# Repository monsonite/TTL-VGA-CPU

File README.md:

# TTL-VGA-CPU
EagleCAD schematics and layout of Marcel van Kervinck's TTL VGA Computer

This is an 8-bit Harvard architecture cpu developed by Marcel van Kervinck - as a practical CPU using simple TTL logic to create a VGA display of 160 x120 pixels in 6-bit colour.

Marcel's original design may be found on HackaDay here: https://hackaday.io/project/20781-8-bit-color-computer-from-ttl

The aim was to develop a practical 8-bit CPU using a minimum of TTL packages - with emphasis on using only those parts that are commonly available.

This repository begins with a transcription of his design to EagleCAD so that the circuit schematic may be better understood and different layout options evaluated.

Marcel has produced a pcb for his design using KiCAD - approximately 9"x6".  However it may be feasible to get the design onto a more compact 6"x4" Eurocard - especially if SMT TTL parts are used.

The files here are in a draft form and are missing some key control signals. They are for information only and do not currently represent a 100% complete transcript of Marcel's design.

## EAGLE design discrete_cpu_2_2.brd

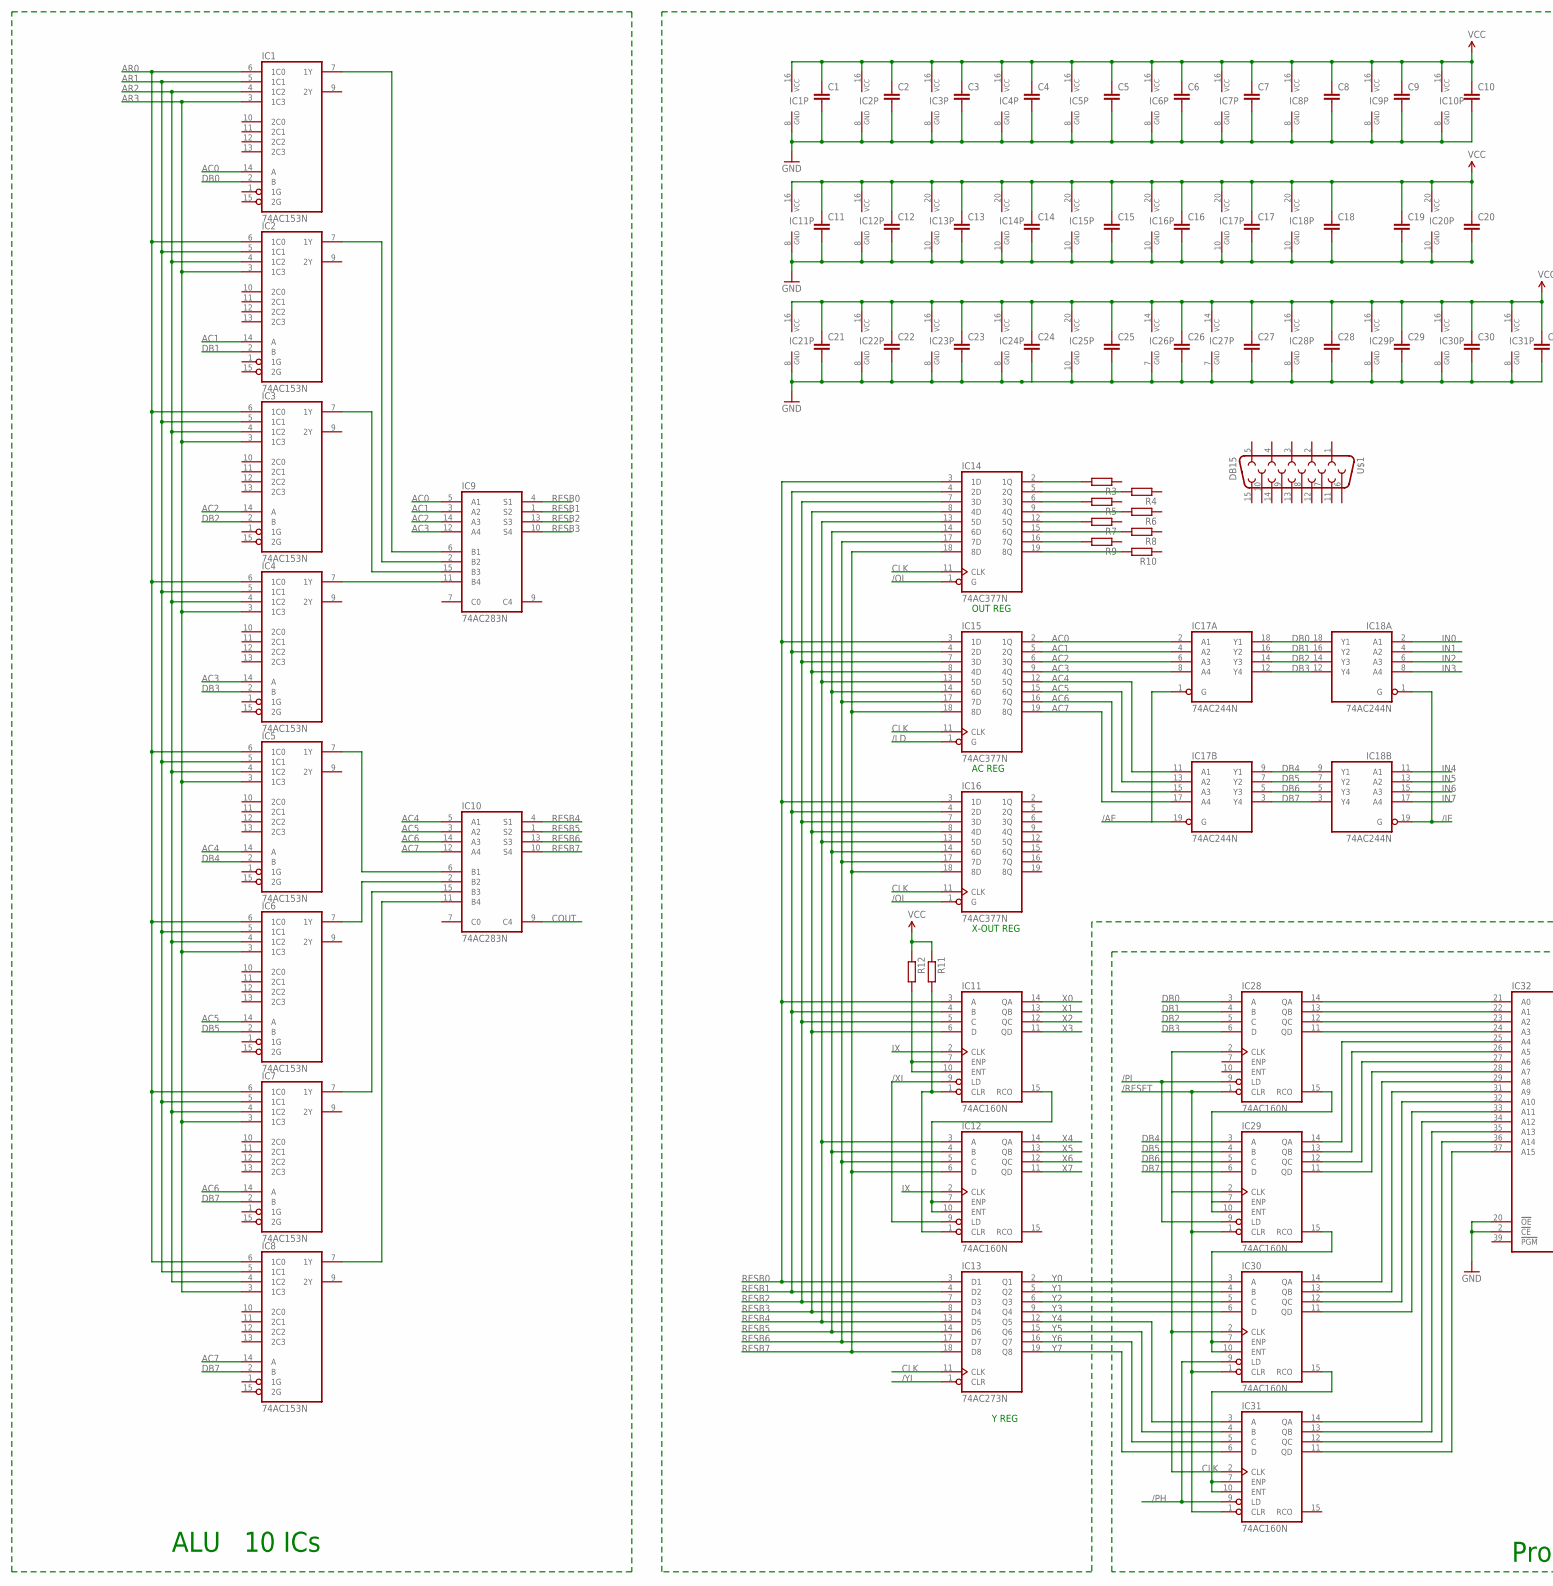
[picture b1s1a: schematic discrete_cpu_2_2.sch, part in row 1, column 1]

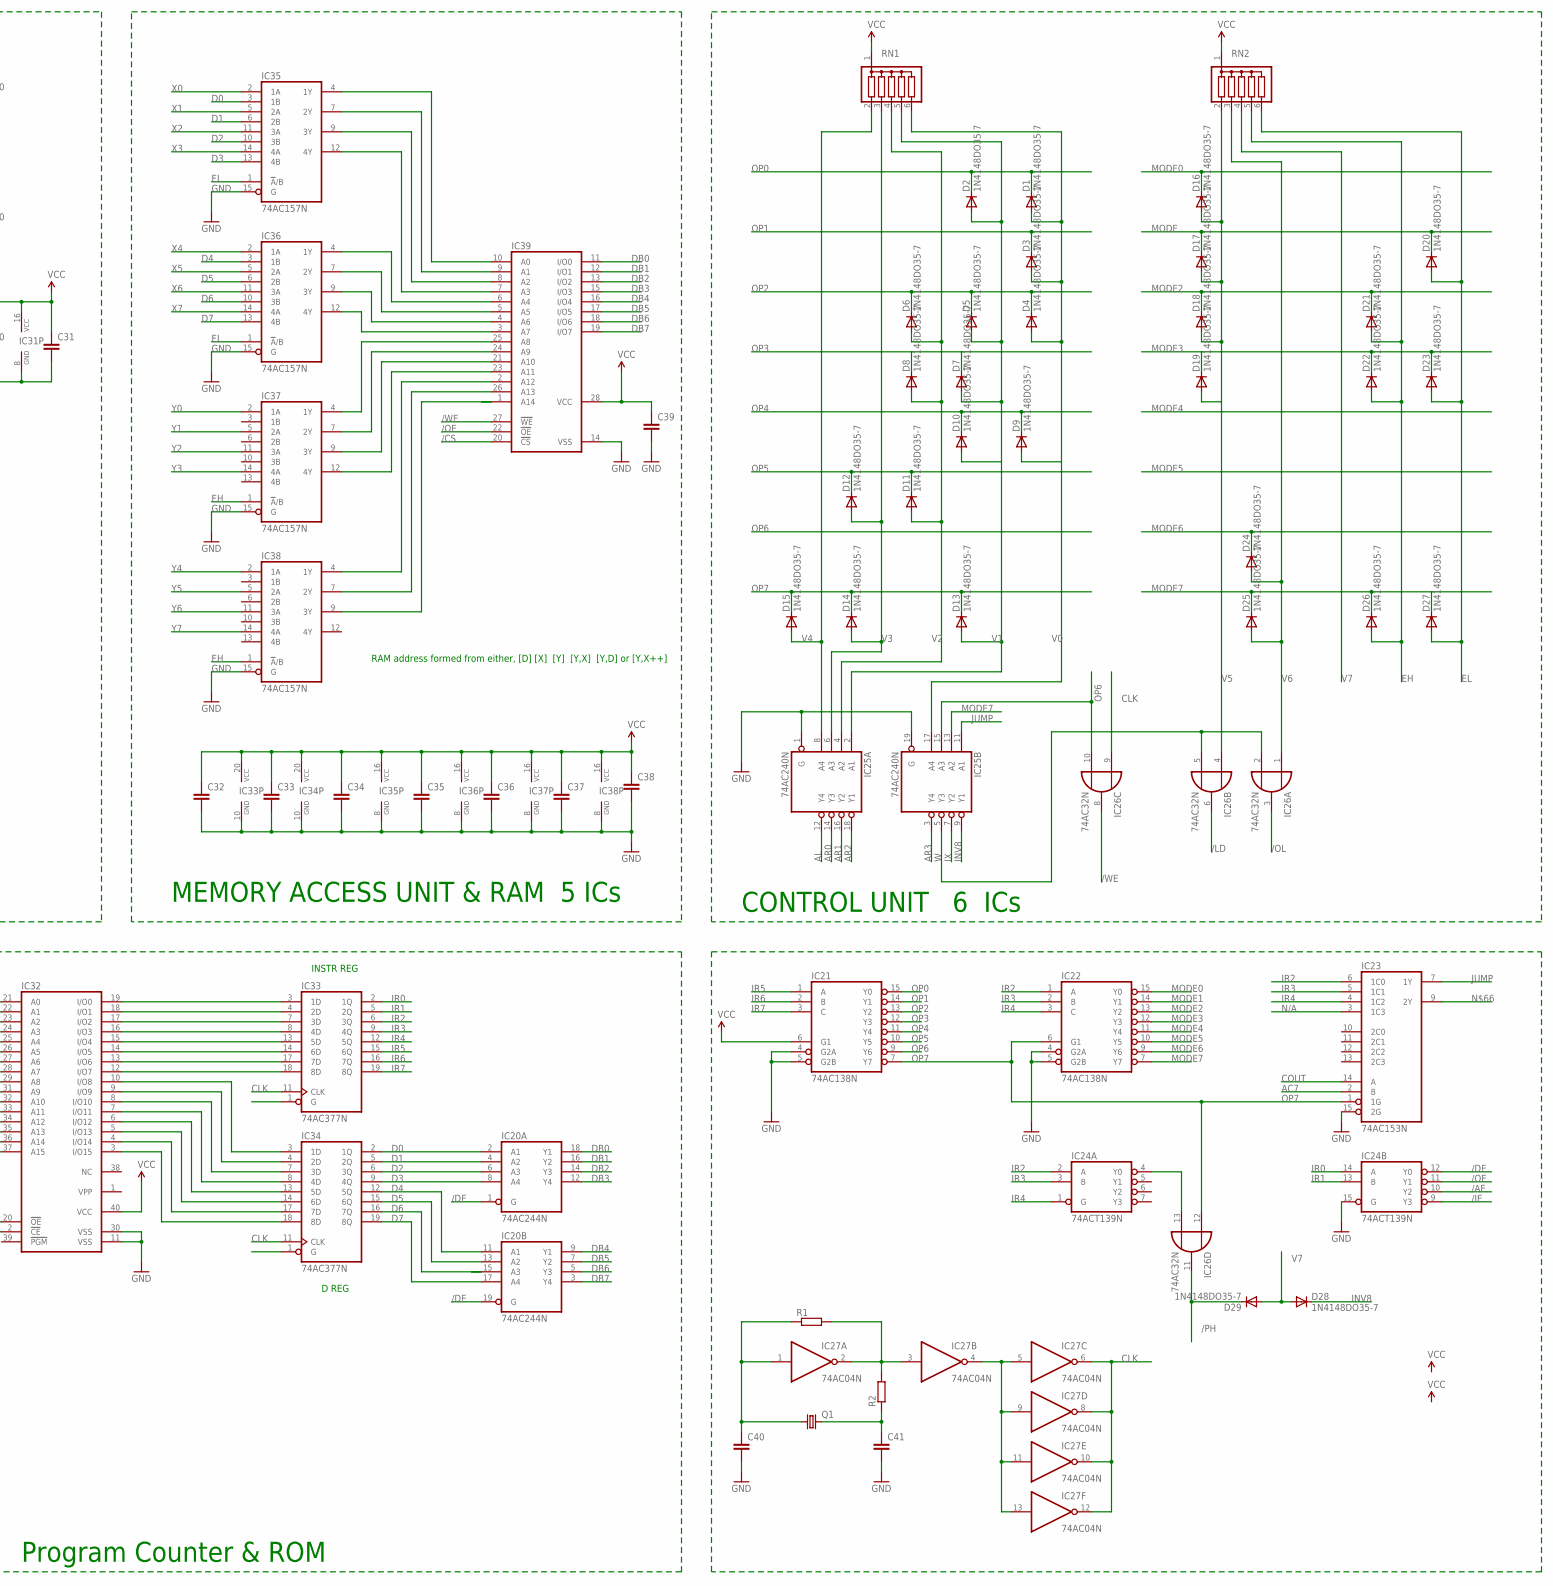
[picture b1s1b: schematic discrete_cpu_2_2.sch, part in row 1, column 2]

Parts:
C1, C2, C3, C4, C5, C6, C7, C8, C9, C10, C11, C12, C13, C14, C15, C16, C17, C18, C19, C20, C21, C22, C23, C24, C25, C26, C27, C28, C29, C30, C31, C32, C33, C34, C35, C36, C37, C38, C39, C40, C41: C-EU025-025X050; C025-025X050
D1, D2, D3, D4, D5, D6, D7, D8, D9, D10, D11, D12, D13, D14, D15, D16, D17, D18, D19, D20, D21, D22, D23, D24, D25, D26, D27, D28, D29: 1N4148DO35-7; DO35-7
IC1, IC2, IC3, IC4, IC5, IC6, IC7, IC8, IC23: 74AC153N; DIL16
IC9, IC10: 74AC283N; DIL16
IC11, IC12, IC28, IC29, IC30, IC31: 74AC160N; DIL16
IC13: 74AC273N; DIL20
IC14, IC15, IC16, IC33, IC34: 74AC377N; DIL20
IC17, IC18, IC20: 74AC244N; DIL20
IC21, IC22: 74AC138N; DIL16
IC24: 74ACT139N; DIL16
IC25: 74AC240N; DIL20
IC26: 74AC32N; DIL14
IC27: 74AC04N; DIL14
IC32: 27C1024HG; DIL40
IC35, IC36, IC37, IC38: 74AC157N; DIL16
IC39: 62256P; DIL28-6
Q1: CRYSTALHC49S; HC49/S
R1, R2, R3, R4, R5, R6, R7, R8, R9, R10, R11, R12: R-EU_0204/7; 0204/7
RN1, RN2: G05R; SIL6
U$1: DB15

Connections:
/AE: IC17.1 (G), IC17.19 (G), IC24.10 (Y2)
/CS: IC39.20 (!CS)
/DE: IC20.1 (G), IC20.19 (G), IC24.12 (Y0)
/IE: IC18.1 (G), IC18.19 (G), IC24.9 (Y3)
/LD: IC15.1 (G), IC26.6 (O)
/OE: IC24.11 (Y1), IC39.22 (!OE)
/OL: IC14.1 (G), IC16.1 (G), IC26.3 (O)
/PH: D29.C, IC26.11 (O), IC30.9 (LD), IC31.9 (LD)
/PL: IC28.9 (LD), IC29.9 (LD)
/RESET: IC28.1 (CLR), IC29.1 (CLR), IC30.1 (CLR), IC31.1 (CLR)
/WE: IC26.8 (O), IC39.27 (!WE)
/XL: IC11.9 (LD), IC12.9 (LD)
/YL: IC13.1 (CLR)
AC0: IC1.14 (A), IC9.5 (A1), IC15.2 (1Q), IC17.2 (A1)
AC1: IC2.14 (A), IC9.3 (A2), IC15.5 (2Q), IC17.4 (A2)
AC2: IC3.14 (A), IC9.14 (A3), IC15.6 (3Q), IC17.6 (A3)
AC3: IC4.14 (A), IC9.12 (A4), IC15.9 (4Q), IC17.8 (A4)
AC4: IC5.14 (A), IC10.5 (A1), IC15.12 (5Q), IC17.11 (A1)
AC5: IC6.14 (A), IC10.3 (A2), IC15.15 (6Q), IC17.13 (A2)
AC6: IC7.14 (A), IC10.14 (A3), IC15.16 (7Q), IC17.15 (A3)
AC7: IC8.14 (A), IC10.12 (A4), IC15.19 (8Q), IC17.17 (A4), IC23.2 (B)
AL: IC25.12 (Y4)
AR0: IC1.6 (1C0), IC2.6 (1C0), IC3.6 (1C0), IC4.6 (1C0), IC5.6 (1C0), IC6.6 (1C0), IC7.6 (1C0), IC8.6 (1C0), IC25.14 (Y3)
AR1: IC1.5 (1C1), IC2.5 (1C1), IC3.5 (1C1), IC4.5 (1C1), IC5.5 (1C1), IC6.5 (1C1), IC7.5 (1C1), IC8.5 (1C1), IC25.16 (Y2)
AR2: IC1.4 (1C2), IC2.4 (1C2), IC3.4 (1C2), IC4.4 (1C2), IC5.4 (1C2), IC6.4 (1C2), IC7.4 (1C2), IC8.4 (1C2), IC25.18 (Y1)
AR3: IC1.3 (1C3), IC2.3 (1C3), IC3.3 (1C3), IC4.3 (1C3), IC5.3 (1C3), IC6.3 (1C3), IC7.3 (1C3), IC8.3 (1C3), IC25.3 (Y4)
CLK: IC13.11 (CLK), IC14.11 (CLK), IC15.11 (CLK), IC16.11 (CLK), IC26.9 (I0), IC27.6 (O), IC27.8 (O), IC27.10 (O), IC27.12 (O), IC28.2 (CLK), IC29.2 (CLK), IC30.2 (CLK), IC31.2 (CLK), IC33.11 (CLK), IC34.11 (CLK)
COUT: IC10.9 (C4), IC23.14 (A)
D0: IC20.2 (A1), IC34.2 (1Q), IC35.3 (1B)
D1: IC20.4 (A2), IC34.5 (2Q), IC35.6 (2B)
D2: IC20.6 (A3), IC34.6 (3Q), IC35.10 (3B)
D3: IC20.8 (A4), IC34.9 (4Q), IC35.13 (4B)
D4: IC20.11 (A1), IC34.12 (5Q), IC36.3 (1B)
D5: IC20.13 (A2), IC34.15 (6Q), IC36.6 (2B)
D6: IC20.15 (A3), IC34.16 (7Q), IC36.10 (3B)
D7: IC20.17 (A4), IC34.19 (8Q), IC36.13 (4B)
DB0: IC1.2 (B), IC17.18 (Y1), IC18.18 (Y1), IC20.18 (Y1), IC28.3 (A), IC39.11 (I/O0)
DB1: IC2.2 (B), IC17.16 (Y2), IC18.16 (Y2), IC20.16 (Y2), IC28.4 (B), IC39.12 (I/O1)
DB2: IC3.2 (B), IC17.14 (Y3), IC18.14 (Y3), IC20.14 (Y3), IC28.5 (C), IC39.13 (I/O2)
DB3: IC4.2 (B), IC17.12 (Y4), IC18.12 (Y4), IC20.12 (Y4), IC28.6 (D), IC39.15 (I/O3)
DB4: IC5.2 (B), IC17.9 (Y1), IC18.9 (Y1), IC20.9 (Y1), IC29.3 (A), IC39.16 (I/O4)
DB5: IC6.2 (B), IC17.7 (Y2), IC18.7 (Y2), IC20.7 (Y2), IC29.4 (B), IC39.17 (I/O5)
DB6: IC17.5 (Y3), IC18.5 (Y3), IC20.5 (Y3), IC29.5 (C), IC39.18 (I/O6)
DB7: IC7.2 (B), IC8.2 (B), IC17.3 (Y4), IC18.3 (Y4), IC20.3 (Y4), IC29.6 (D), IC39.19 (I/O7)
EH: D21.A, D22.A, D26.A, IC37.1 (!A!/B), IC38.1 (!A!/B), RN2.5
EL: D20.A, D23.A, D27.A, IC35.1 (!A!/B), IC36.1 (!A!/B), RN2.6
GND: C1.2, C2.2, C3.2, C4.2, C5.2, C6.2, C7.2, C8.2, C9.2, C10.2, C11.2, C12.2, C13.2, C14.2, C15.2, C16.2, C17.2, C18.2, C19.2, C20.2, C21.2, C22.2, C23.2, C24.2, C25.2, C26.2, C27.2, C28.2, C29.2, C30.2, C31.2, C32.2, C33.2, C34.2, C35.2, C36.2, C37.2, C38.2, C39.2, C40.2, C41.2, IC1.8 (GND), IC2.8 (GND), IC3.8 (GND), IC4.8 (GND), IC5.8 (GND), IC6.8 (GND), IC7.8 (GND), IC8.8 (GND), IC9.8 (GND), IC10.8 (GND), IC11.8 (GND), IC12.8 (GND), IC13.10 (GND), IC14.10 (GND), IC15.10 (GND), IC16.10 (GND), IC17.10 (GND), IC18.10 (GND), IC20.10 (GND), IC21.4 (G2A), IC21.5 (G2B), IC21.8 (GND), IC22.4 (G2A), IC22.5 (G2B), IC22.8 (GND), IC23.8 (GND), IC23.15 (2G), IC24.8 (GND), IC24.15 (G), IC25.1 (G), IC25.10 (GND), IC25.19 (G), IC26.7 (GND), IC27.7 (GND), IC28.8 (GND), IC29.8 (GND), IC30.8 (GND), IC31.8 (GND), IC32.2 (!CE), IC32.11 (VSS), IC32.20 (!OE), IC32.30 (VSS), IC33.10 (GND), IC34.10 (GND), IC35.8 (GND), IC35.15 (G), IC36.8 (GND), IC36.15 (G), IC37.8 (GND), IC37.15 (G), IC38.8 (GND), IC38.15 (G), IC39.14 (VSS)
IN0: IC18.2 (A1)
IN1: IC18.4 (A2)
IN2: IC18.6 (A3)
IN3: IC18.8 (A4)
IN4: IC18.11 (A1)
IN5: IC18.13 (A2)
IN6: IC18.15 (A3)
IN7: IC18.17 (A4)
INV8: D28.C, IC25.9 (Y1)
IR0: IC24.14 (A), IC33.2 (1Q)
IR1: IC24.13 (B), IC33.5 (2Q)
IR2: IC22.1 (A), IC23.6 (1C0), IC24.2 (A), IC33.6 (3Q)
IR3: IC22.2 (B), IC23.5 (1C1), IC24.3 (B), IC33.9 (4Q)
IR4: IC22.3 (C), IC23.4 (1C2), IC24.1 (G), IC33.12 (5Q)
IR5: IC21.1 (A), IC33.15 (6Q)
IR6: IC21.2 (B), IC33.16 (7Q)
IR7: IC21.3 (C), IC33.19 (8Q)
IX: IC11.2 (CLK), IC12.2 (CLK), IC25.7 (Y2)
JUMP: IC23.7 (1Y), IC25.11 (A1)
MODE: D17.C, D20.C
MODE0: D16.C, IC22.15 (Y0)
MODE1: IC22.14 (Y1)
MODE2: D18.C, D21.C, IC22.13 (Y2)
MODE3: D19.C, D22.C, D23.C, IC22.12 (Y3)
MODE4: IC22.11 (Y4)
MODE5: IC22.10 (Y5)
MODE6: D24.C, IC22.9 (Y6)
MODE7: D25.C, D26.C, D27.C, IC22.7 (Y7), IC25.13 (A2)
unnamed: IC8.7 (1Y), IC10.11 (B4)
unnamed: IC7.7 (1Y), IC10.15 (B3)
unnamed: IC6.7 (1Y), IC10.2 (B2)
unnamed: IC5.7 (1Y), IC10.6 (B1)
unnamed: IC4.7 (1Y), IC9.11 (B4)
unnamed: IC24.4 (Y0), IC26.13 (I1)
unnamed: IC3.7 (1Y), IC9.15 (B3)
unnamed: IC2.7 (1Y), IC9.2 (B2)
unnamed: IC1.7 (1Y), IC9.6 (B1)
unnamed: C40.1, IC27.1 (I), Q1.1, R1.1
unnamed: IC27.2 (O), IC27.3 (I), R1.2, R2.2
unnamed: C41.1, Q1.2, R2.1
unnamed: IC27.4 (O), IC27.5 (I), IC27.9 (I), IC27.11 (I), IC27.13 (I)
unnamed: IC11.7 (ENP), IC11.10 (ENT), R12.2
unnamed: IC11.1 (CLR), IC12.1 (CLR), R11.2
unnamed: IC11.15 (RCO), IC12.7 (ENP), IC12.10 (ENT)
unnamed: IC28.15 (RCO), IC29.7 (ENP), IC29.10 (ENT)
unnamed: IC29.15 (RCO), IC30.7 (ENP), IC30.10 (ENT)
unnamed: IC30.15 (RCO), IC31.7 (ENP), IC31.10 (ENT)
unnamed: IC14.2 (1Q), R3.2
unnamed: IC14.5 (2Q), R4.2
unnamed: IC14.6 (3Q), R5.2
unnamed: IC14.9 (4Q), R6.2
unnamed: IC14.12 (5Q), R7.2
unnamed: IC14.15 (6Q), R8.2
unnamed: IC14.16 (7Q), R9.2
unnamed: IC14.19 (8Q), R10.2
unnamed: IC28.14 (QA), IC32.21 (A0)
unnamed: IC28.13 (QB), IC32.22 (A1)
unnamed: IC28.12 (QC), IC32.23 (A2)
unnamed: IC28.11 (QD), IC32.24 (A3)
unnamed: IC29.14 (QA), IC32.25 (A4)
unnamed: IC29.13 (QB), IC32.26 (A5)
unnamed: IC29.12 (QC), IC32.27 (A6)
unnamed: IC29.11 (QD), IC32.28 (A7)
unnamed: IC30.14 (QA), IC32.29 (A8)
unnamed: IC30.13 (QB), IC32.31 (A9)
unnamed: IC30.12 (QC), IC32.32 (A10)
unnamed: IC30.11 (QD), IC32.33 (A11)
unnamed: IC31.14 (QA), IC32.34 (A12)
unnamed: IC31.13 (QB), IC32.35 (A13)
unnamed: IC31.12 (QC), IC32.36 (A14)
unnamed: IC31.11 (QD), IC32.37 (A15)
unnamed: IC35.4 (1Y), IC39.10 (A0)
unnamed: IC35.7 (2Y), IC39.9 (A1)
unnamed: IC35.9 (3Y), IC39.8 (A2)
unnamed: IC35.12 (4Y), IC39.7 (A3)
unnamed: IC36.4 (1Y), IC39.6 (A4)
unnamed: IC36.7 (2Y), IC39.5 (A5)
unnamed: IC36.9 (3Y), IC39.4 (A6)
unnamed: IC36.12 (4Y), IC39.3 (A7)
unnamed: IC32.19 (I/O0), IC33.3 (1D)
unnamed: IC32.18 (I/O1), IC33.4 (2D)
unnamed: IC32.17 (I/O2), IC33.7 (3D)
unnamed: IC32.16 (I/O3), IC33.8 (4D)
unnamed: IC32.15 (I/O4), IC33.13 (5D)
unnamed: IC32.14 (I/O5), IC33.14 (6D)
unnamed: IC32.13 (I/O6), IC33.17 (7D)
unnamed: IC32.12 (I/O7), IC33.18 (8D)
unnamed: IC32.10 (I/O8), IC34.3 (1D)
unnamed: IC32.9 (I/O9), IC34.4 (2D)
unnamed: IC32.8 (I/O10), IC34.7 (3D)
unnamed: IC32.7 (I/O11), IC34.8 (4D)
unnamed: IC32.6 (I/O12), IC34.13 (5D)
unnamed: IC32.5 (I/O13), IC34.14 (6D)
unnamed: IC32.4 (I/O14), IC34.17 (7D)
unnamed: IC32.3 (I/O15), IC34.18 (8D)
unnamed: IC37.4 (1Y), IC39.25 (A8)
unnamed: IC37.7 (2Y), IC39.24 (A9)
unnamed: IC37.9 (3Y), IC39.21 (A10)
unnamed: IC37.12 (4Y), IC39.23 (A11)
unnamed: IC38.4 (1Y), IC39.2 (A12)
unnamed: IC38.7 (2Y), IC39.26 (A13)
unnamed: IC38.9 (3Y), IC39.1 (A14)
N/A: IC23.3 (1C3)
OP0: D1.C, D2.C, IC21.15 (Y0)
OP1: D3.C, IC21.14 (Y1)
OP2: D4.C, D5.C, D6.C, IC21.13 (Y2)
OP3: D7.C, D8.C, IC21.12 (Y3)
OP4: D9.C, D10.C, IC21.11 (Y4)
OP5: D11.C, D12.C, IC21.10 (Y5)
OP6: IC21.9 (Y6), IC25.15 (A3), IC26.10 (I1)
OP7: D13.C, D14.C, D15.C, IC21.7 (Y7), IC22.6 (G1), IC23.1 (1G), IC26.12 (I0)
RESB0: IC9.4 (S1), IC11.3 (A), IC13.3 (D1), IC14.3 (1D), IC15.3 (1D), IC16.3 (1D)
RESB1: IC9.1 (S2), IC11.4 (B), IC13.4 (D2), IC14.4 (2D), IC15.4 (2D), IC16.4 (2D)
RESB2: IC9.13 (S3), IC11.5 (C), IC13.7 (D3), IC14.7 (3D), IC15.7 (3D), IC16.7 (3D)
RESB3: IC9.10 (S4), IC11.6 (D), IC13.8 (D4), IC14.8 (4D), IC15.8 (4D), IC16.8 (4D)
RESB4: IC10.4 (S1), IC12.3 (A), IC13.13 (D5), IC14.13 (5D), IC15.13 (5D), IC16.13 (5D)
RESB5: IC10.1 (S2), IC12.4 (B), IC13.14 (D6), IC14.14 (6D), IC15.14 (6D), IC16.14 (6D)
RESB6: IC10.13 (S3), IC12.5 (C), IC13.17 (D7), IC14.17 (7D), IC15.17 (7D), IC16.17 (7D)
RESB7: IC10.10 (S4), IC12.6 (D), IC13.18 (D8), IC14.18 (8D), IC15.18 (8D), IC16.18 (8D)
V0: D1.A, D3.A, D4.A, D9.A, IC25.17 (A4), RN1.6
V1: D2.A, D5.A, D7.A, D10.A, D13.A, IC25.2 (A1), RN1.5
V2: D6.A, D8.A, D11.A, IC25.4 (A2), RN1.4
V3: D12.A, D14.A, IC25.6 (A3), RN1.3
V4: D15.A, IC25.8 (A4), RN1.2
V5: D16.A, D17.A, D18.A, D19.A, IC26.4 (I0), RN2.2
V6: D24.A, D25.A, IC26.1 (I0), RN2.3
V7: D28.A, D29.A, RN2.4
VCC: C1.1, C2.1, C3.1, C4.1, C5.1, C6.1, C7.1, C8.1, C9.1, C10.1, C11.1, C12.1, C13.1, C14.1, C15.1, C16.1, C17.1, C18.1, C19.1, C20.1, C21.1, C22.1, C23.1, C24.1, C25.1, C26.1, C27.1, C28.1, C29.1, C30.1, C31.1, C32.1, C33.1, C34.1, C35.1, C36.1, C37.1, C38.1, C39.1, IC1.16 (VCC), IC2.16 (VCC), IC3.16 (VCC), IC4.16 (VCC), IC5.16 (VCC), IC6.16 (VCC), IC7.16 (VCC), IC8.16 (VCC), IC9.16 (VCC), IC10.16 (VCC), IC11.16 (VCC), IC12.16 (VCC), IC13.20 (VCC), IC14.20 (VCC), IC15.20 (VCC), IC16.20 (VCC), IC17.20 (VCC), IC18.20 (VCC), IC20.20 (VCC), IC21.6 (G1), IC21.16 (VCC), IC22.16 (VCC), IC23.16 (VCC), IC24.16 (VCC), IC25.20 (VCC), IC26.14 (VCC), IC27.14 (VCC), IC28.16 (VCC), IC29.16 (VCC), IC30.16 (VCC), IC31.16 (VCC), IC32.40 (VCC), IC33.20 (VCC), IC34.20 (VCC), IC35.16 (VCC), IC36.16 (VCC), IC37.16 (VCC), IC38.16 (VCC), IC39.28 (VCC), R11.1, R12.1, RN1.1, RN2.1
W: IC25.5 (Y3), IC26.2 (I1), IC26.5 (I1)
X0: IC11.14 (QA), IC35.2 (1A)
X1: IC11.13 (QB), IC35.5 (2A)
X2: IC11.12 (QC), IC35.11 (3A)
X3: IC11.11 (QD), IC35.14 (4A)
X4: IC12.14 (QA), IC36.2 (1A)
X5: IC12.13 (QB), IC36.5 (2A)
X6: IC12.12 (QC), IC36.11 (3A)
X7: IC12.11 (QD), IC36.14 (4A)
Y0: IC13.2 (Q1), IC30.3 (A), IC37.2 (1A)
Y1: IC13.5 (Q2), IC30.4 (B), IC37.5 (2A)
Y2: IC13.6 (Q3), IC30.5 (C), IC37.11 (3A)
Y3: IC13.9 (Q4), IC30.6 (D), IC37.14 (4A)
Y4: IC13.12 (Q5), IC31.3 (A), IC38.2 (1A)
Y5: IC13.15 (Q6), IC31.4 (B), IC38.5 (2A)
Y6: IC13.16 (Q7), IC31.5 (C), IC38.11 (3A)
Y7: IC13.19 (Q8), IC31.6 (D), IC38.14 (4A)

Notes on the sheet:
Program Counter & ROM
MEMORY ACCESS UNIT & RAM 5 ICs
ALU 10 ICs
Y REG
X-OUT REG
AC REG
OUT REG
D REG
INSTR REG
CONTROL UNIT 6 ICs
RAM address formed from either, [D] [X] [Y] [Y,X] [Y,D] or [Y,X++]

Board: 2 copper layers, 124 parts (0 on the bottom side), 177 nets, no tracks yet.

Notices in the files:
parts and their libraries:
SparkFun-Connectors: Licensing: Creative Commons ShareAlike 4.0 International - https://creativecommons.org/licenses/by-sa/4.0
